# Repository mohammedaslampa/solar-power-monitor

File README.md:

# solar-power-monitor
monitoring solar power

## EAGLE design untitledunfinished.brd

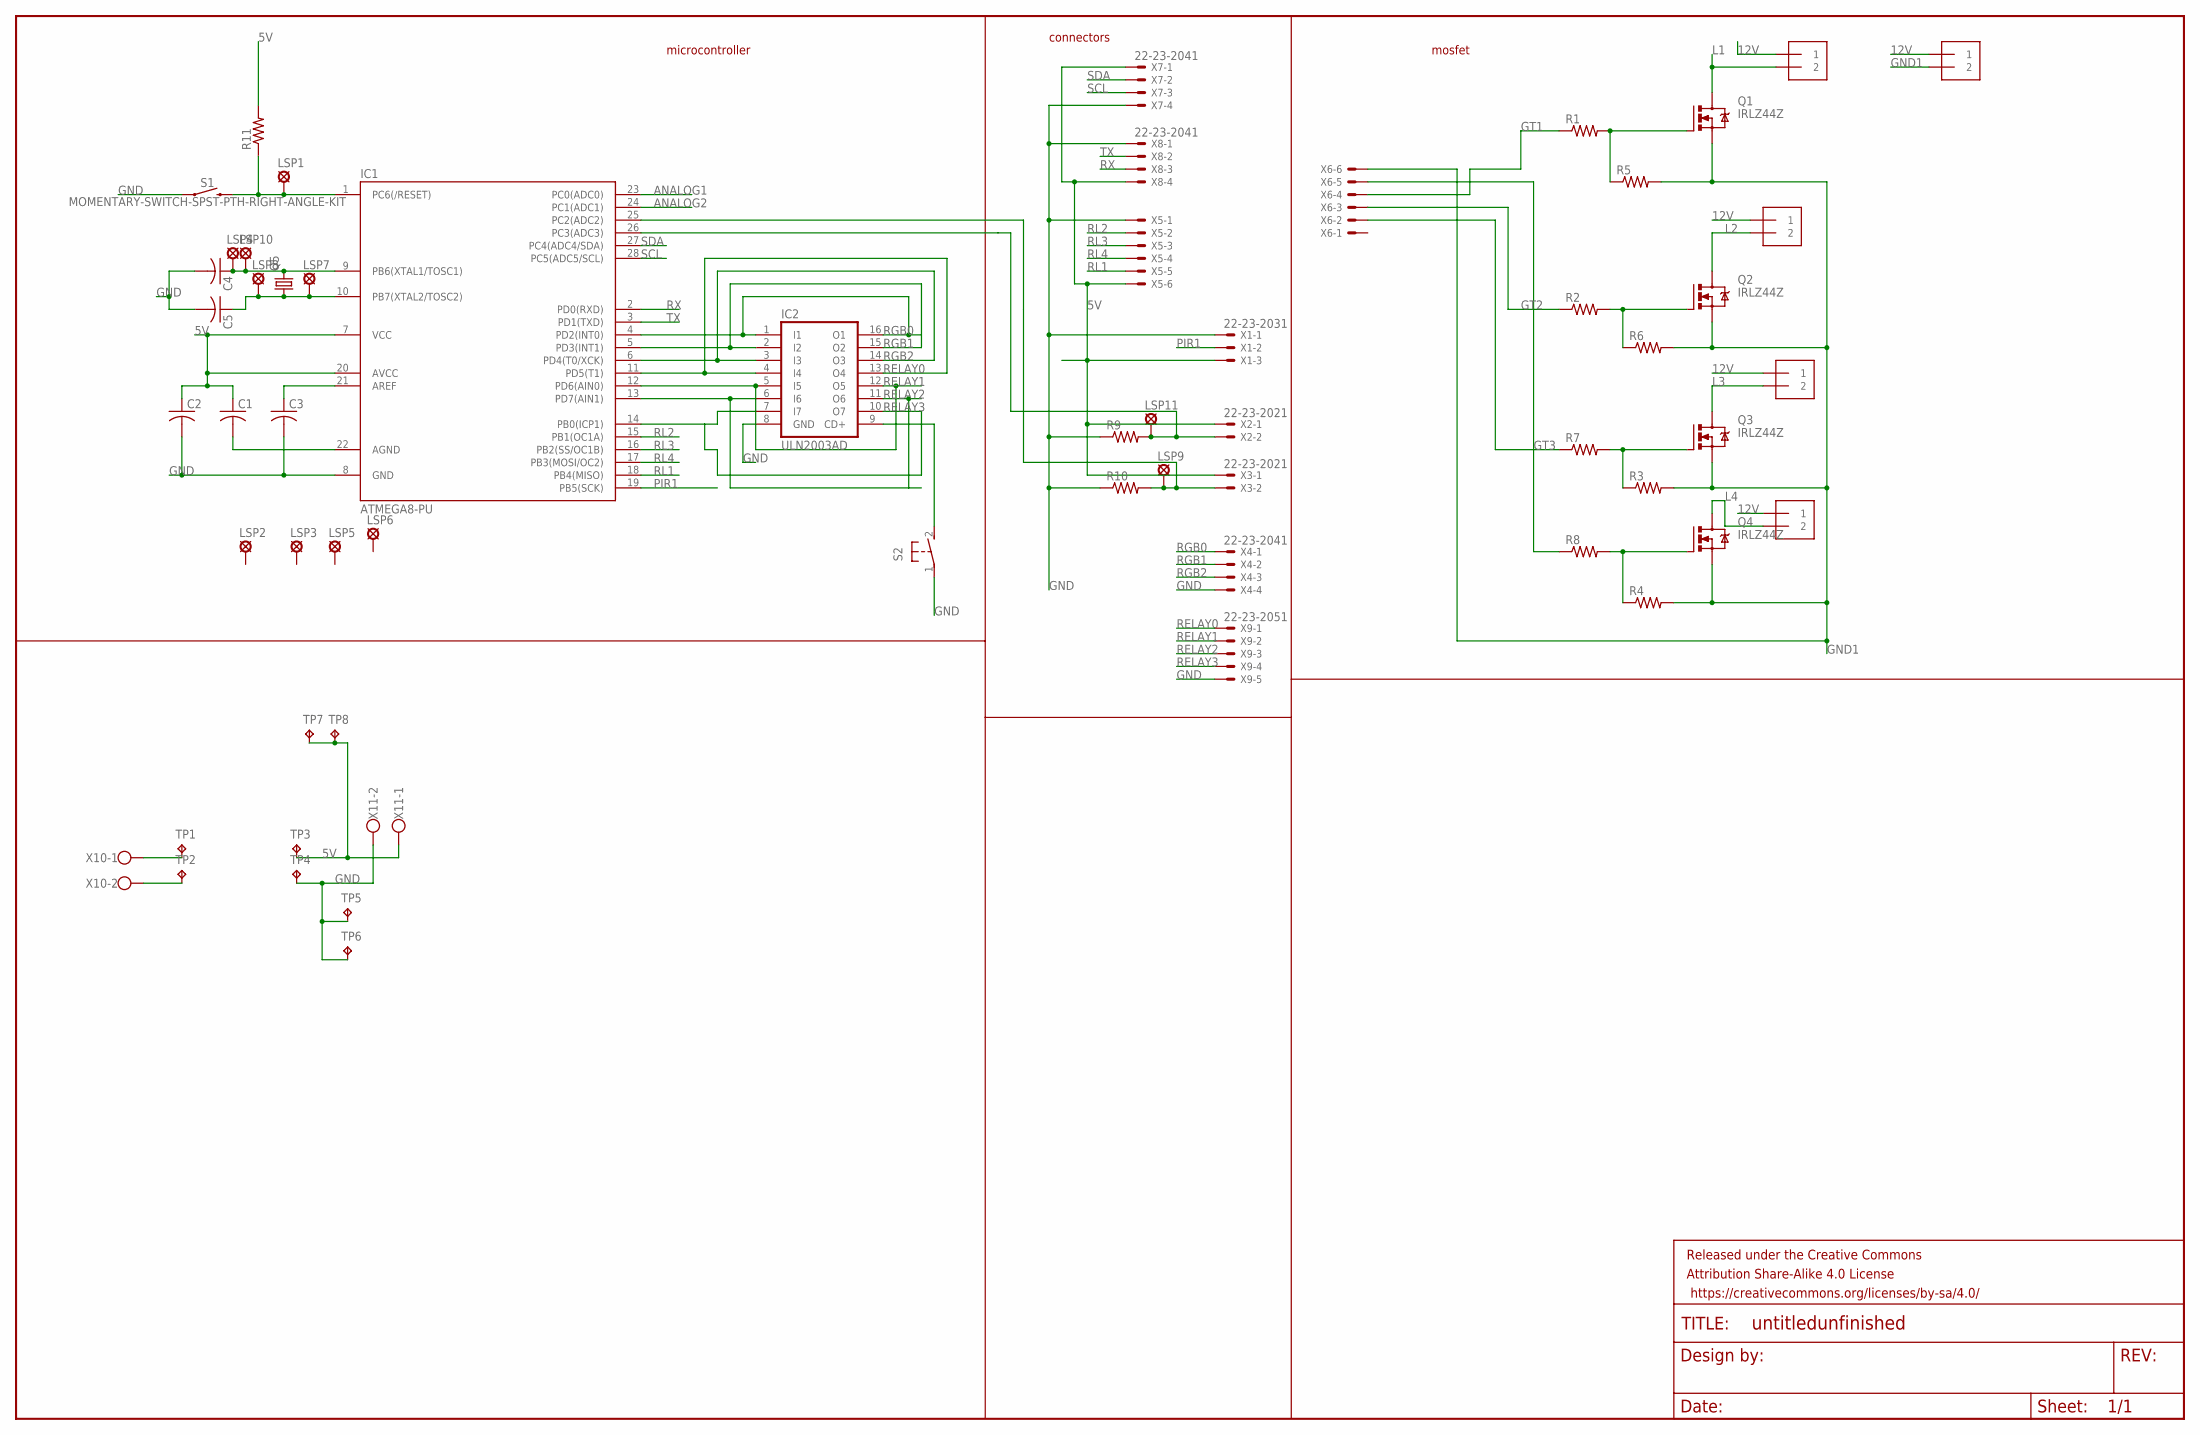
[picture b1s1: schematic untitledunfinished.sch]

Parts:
C1, C2, C3: C-US050-025X075; C050-025X075
C4, C5: C-US050-024X044; C050-024X044
FRAME1: FRAME-LEDGER; CREATIVE_COMMONS
IC1: ATMEGA8-PU; DIL28-3
IC2: ULN2003AD; SO16
J1, J2, J3, J4, J5: 1X2-3.5MM
LSP1, LSP2, LSP3, LSP4, LSP5, LSP6, LSP7, LSP8, LSP9, LSP10, LSP11: SE11
Q1, Q2, Q3, Q4: IRLZ44Z; TO220BH
Q5: CRYSTALHC49U-V; HC49U-V
R1, R2, R3, R4, R5, R6, R7, R8, R11: R-US_0207/10; 0207/10
R9, R10: R-US_0207/15; 0207/15
S1: MOMENTARY-SWITCH-SPST-PTH-RIGHT-ANGLE-KIT; TACTILE_SWITCH_PTH_RIGHT_ANGLE_KIT
S2: 31-XX; B3F-31XX
TP1, TP2, TP3, TP4: TPPAD1-20Y; P1-20Y
TP5, TP6, TP7, TP8: TPPAD1-13Y; P1-13Y
X1: 22-23-2031
X2, X3: 22-23-2021
X4, X7, X8: 22-23-2041
X5, X6: 22-23-2061
X9: 22-23-2051
X10, X11: W237-102

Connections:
5V: C1.1, C2.1, IC1.7 (VCC), IC1.20 (AVCC), R11.2, TP3.TP, TP7.TP, TP8.TP, X1.3, X2.1, X3.1, X5.6, X7.1, X8.4, X11.1
12V: J1.1, J2.1, J3.1, J4.1, J5.1
ANALOG1: IC1.23 (PC0(ADC0))
ANALOG2: IC1.24 (PC1(ADC1))
GND: C2.2, C3.2, C4.2, C5.2, IC1.8 (GND), IC2.8 (GND), R9.1, R10.1, S1.1, S2.1, TP4.TP, TP5.TP, TP6.TP, X1.1, X4.4, X5.1, X7.4, X8.1, X9.5, X11.2
GND1: J5.2, Q1.S, Q2.S, Q3.S, Q4.S, R3.2, R4.2, R5.2, R6.2, X6.6
GT1: R1.1, X6.4
GT2: R2.1, X6.3
GT3: R7.1, X6.2
L1: J1.2, Q1.D
L2: J2.2, Q2.D
L3: J3.2, Q3.D
L4: J4.2, Q4.D
unnamed: Q1.G, R1.2, R5.1
unnamed: R8.1, X6.5
unnamed: Q2.G, R2.2, R6.1
unnamed: C1.2, IC1.22 (AGND)
unnamed: Q3.G, R3.1, R7.2
unnamed: C3.1, IC1.21 (AREF)
unnamed: Q4.G, R4.1, R8.2
unnamed: TP1.TP, X10.1
unnamed: IC1.25 (PC2(ADC2)), LSP9.MP, R10.2, X3.2
unnamed: IC1.1 (PC6(/RESET)), LSP1.MP, R11.1, S1.2
unnamed: C4.1, IC1.9 (PB6(XTAL1/TOSC1)), LSP4.MP, LSP10.MP, Q5.2
unnamed: C5.1, IC1.10 (PB7(XTAL2/TOSC2)), LSP7.MP, LSP8.MP, Q5.1
unnamed: IC2.9 (CD+), S2.2 (S)
unnamed: IC1.26 (PC3(ADC3)), LSP11.MP, R9.2, X2.2
unnamed: TP2.TP, X10.2
PIR1: IC1.19 (PB5(SCK)), X1.2
RELAY0: IC1.11 (PD5(T1)), IC2.4 (I4), IC2.13 (O4), X9.1
RELAY1: IC1.12 (PD6(AIN0)), IC2.5 (I5), IC2.12 (O5), X9.2
RELAY2: IC1.13 (PD7(AIN1)), IC2.6 (I6), IC2.11 (O6), X9.3
RELAY3: IC1.14 (PB0(ICP1)), IC2.7 (I7), IC2.10 (O7), X9.4
RGB0: IC1.4 (PD2(INT0)), IC2.1 (I1), IC2.16 (O1), X4.1
RGB1: IC1.5 (PD3(INT1)), IC2.2 (I2), IC2.15 (O2), X4.2
RGB2: IC1.6 (PD4(T0/XCK)), IC2.3 (I3), IC2.14 (O3), X4.3
RL1: IC1.18 (PB4(MISO)), X5.5
RL2: IC1.15 (PB1(OC1A)), X5.2
RL3: IC1.16 (PB2(SS/OC1B)), X5.3
RL4: IC1.17 (PB3(MOSI/OC2)), X5.4
RX: IC1.2 (PD0(RXD)), X8.3
SCL: IC1.28 (PC5(ADC5/SCL)), X7.3
SDA: IC1.27 (PC4(ADC4/SDA)), X7.2
TX: IC1.3 (PD1(TXD)), X8.2

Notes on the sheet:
microcontroller
mosfet
connectors

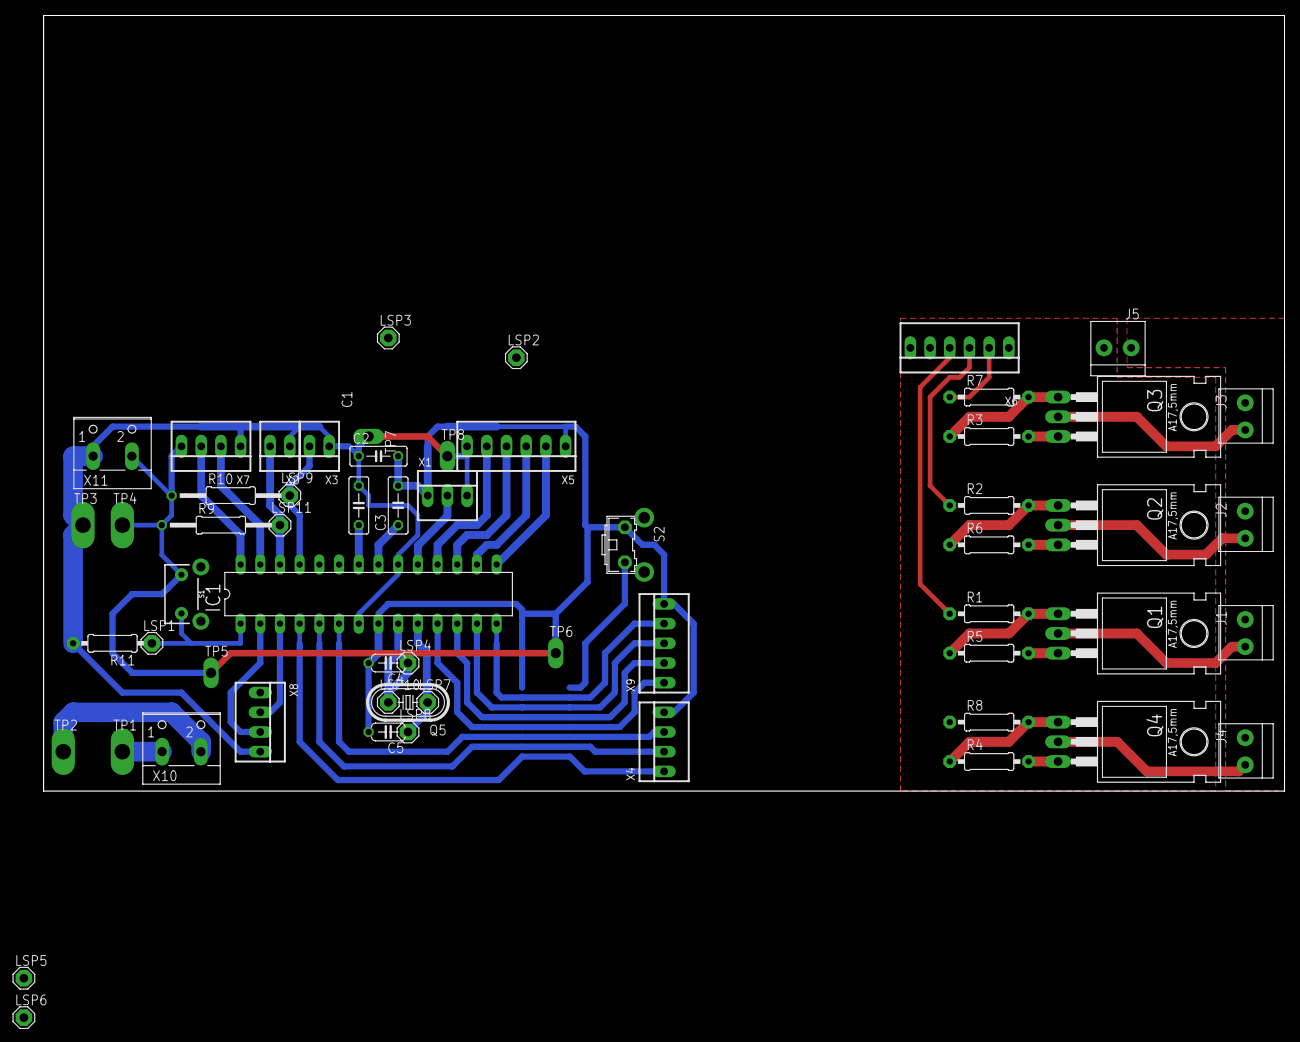
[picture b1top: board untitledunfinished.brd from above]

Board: 2 copper layers, 160.0 x 100.0 mm, 61 parts (1 on the bottom side), 42 nets.

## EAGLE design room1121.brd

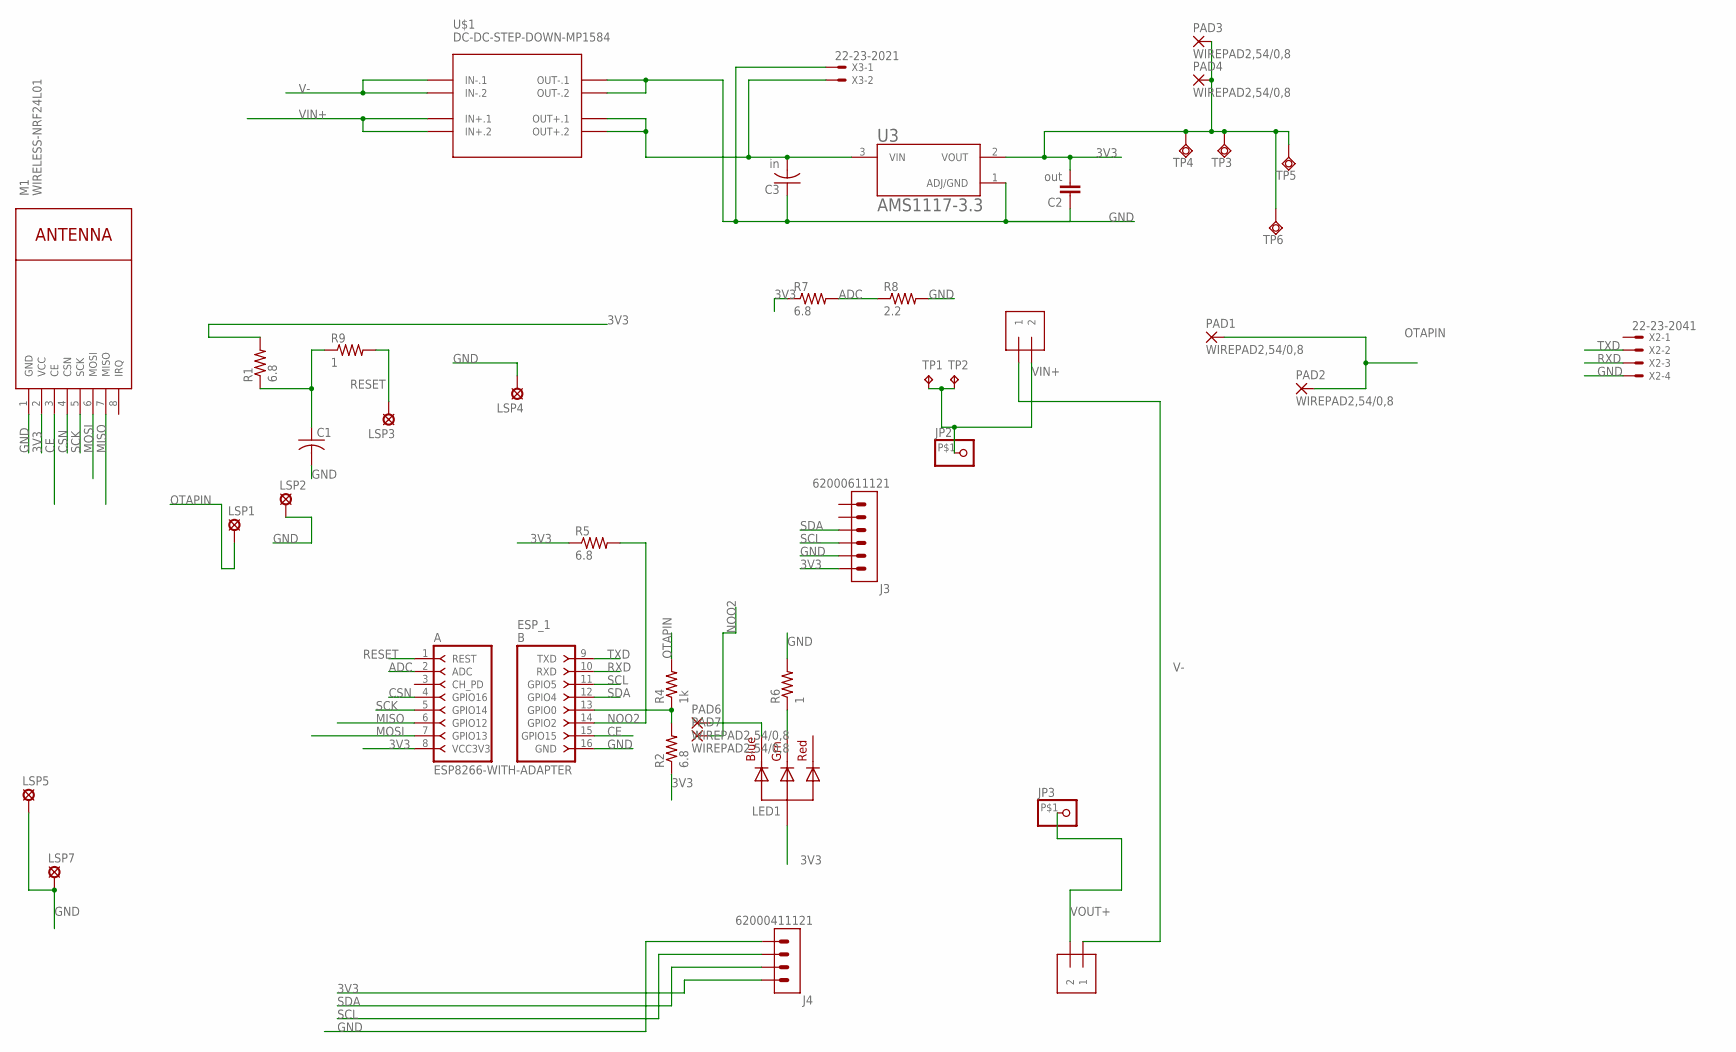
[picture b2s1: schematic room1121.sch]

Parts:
C1: C-US025-040X050; C025-040X050
C2: out; C025-060X050
C3: in; C075-032X103
ESP_1: ESP8266-WITH-ADAPTER; ESP8266-ADAPTER
J1, J2: 1X2-3.5MM
J3: 62000611121
J4: 62000411121
JP2, JP3: PINHD-1X1-BIGPOGO; 1X1-BIGPOGO
LED1: RGBLED_CA-5MM; LED5MMRGB
LSP1, LSP2, LSP3, LSP4: SE14
LSP5, LSP7: MCS10B
M1: WIRELESS-NRF24L01
PAD1, PAD2, PAD3, PAD4, PAD6, PAD7: WIREPAD2,54/0,8; 2,54/0,8
R1, R2: 6.8; 0207/15
R4: 1k; 0207/15
R5, R7: 6.8; 0207/12
R6: 1; 0207/10
R8: 2.2; 0207/15
R9: 1; 0207/12
TP1, TP2: TPPAD1-20Y; P1-20Y
TP3, TP4, TP5, TP6: TPSQPAD1-13Y; P1-13Y
U3: AMS1117-3.3; SOT229P700X180-4N
U$1: DC-DC-STEP-DOWN-MP1584
X2: 22-23-2041
X3: 22-23-2021

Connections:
3V3: C2.2, ESP_1.8 (VCC3V3), J3.1, J4.1, LED1.2 (VCC), M1.2 (VCC), PAD3.1, PAD4.1, R1.2, R2.1, R5.1, R7.1, TP3.TP, TP4.TP, TP5.TP, TP6.TP, U3.2 (VOUT)
ADC: ESP_1.2 (ADC), R7.2, R8.1
CE: ESP_1.15 (GPIO15), M1.3 (CE)
CSN: ESP_1.4 (GPIO16), M1.4 (CSN)
GND: C1.2, C2.1, C3.1, ESP_1.16 (GND), J3.2, J4.4, LSP2.MP, LSP4.MP, LSP5.MP, LSP7.MP, M1.1 (GND), R6.2, R8.2, U3.1 (ADJ/GND), U$1.OUT-.1, U$1.OUT-.2, X2.4, X3.1
MISO: ESP_1.6 (GPIO12), M1.7 (MISO)
MOSI: ESP_1.7 (GPIO13), M1.6 (MOSI)
unnamed: LED1.3 (GREEN), R6.1
unnamed: ESP_1.13 (GPIO0), R2.2, R4.1
unnamed: C3.2, U3.3 (VIN), U$1.OUT+.1, U$1.OUT+.2, X3.2
unnamed: LED1.4 (BLUE), PAD6.1
unnamed: LSP3.MP, R9.2
NOO2: ESP_1.14 (GPIO2), PAD7.1, R5.2
OTAPIN: LSP1.MP, PAD1.1, PAD2.1, R4.2
RESET: C1.1, ESP_1.1 (REST), R1.1, R9.1
RXD: ESP_1.10 (RXD), X2.3
SCK: ESP_1.5 (GPIO14), M1.5 (SCK)
SCL: ESP_1.11 (GPIO5), J3.3, J4.3
SDA: ESP_1.12 (GPIO4), J3.4, J4.2
TXD: ESP_1.9 (TXD), X2.2
V-: J1.1, J2.1, U$1.IN-.1, U$1.IN-.2
VIN+: J2.2, JP2.P$1, TP1.TP, TP2.TP, U$1.IN+.1, U$1.IN+.2
VOUT+: J1.2, JP3.P$1

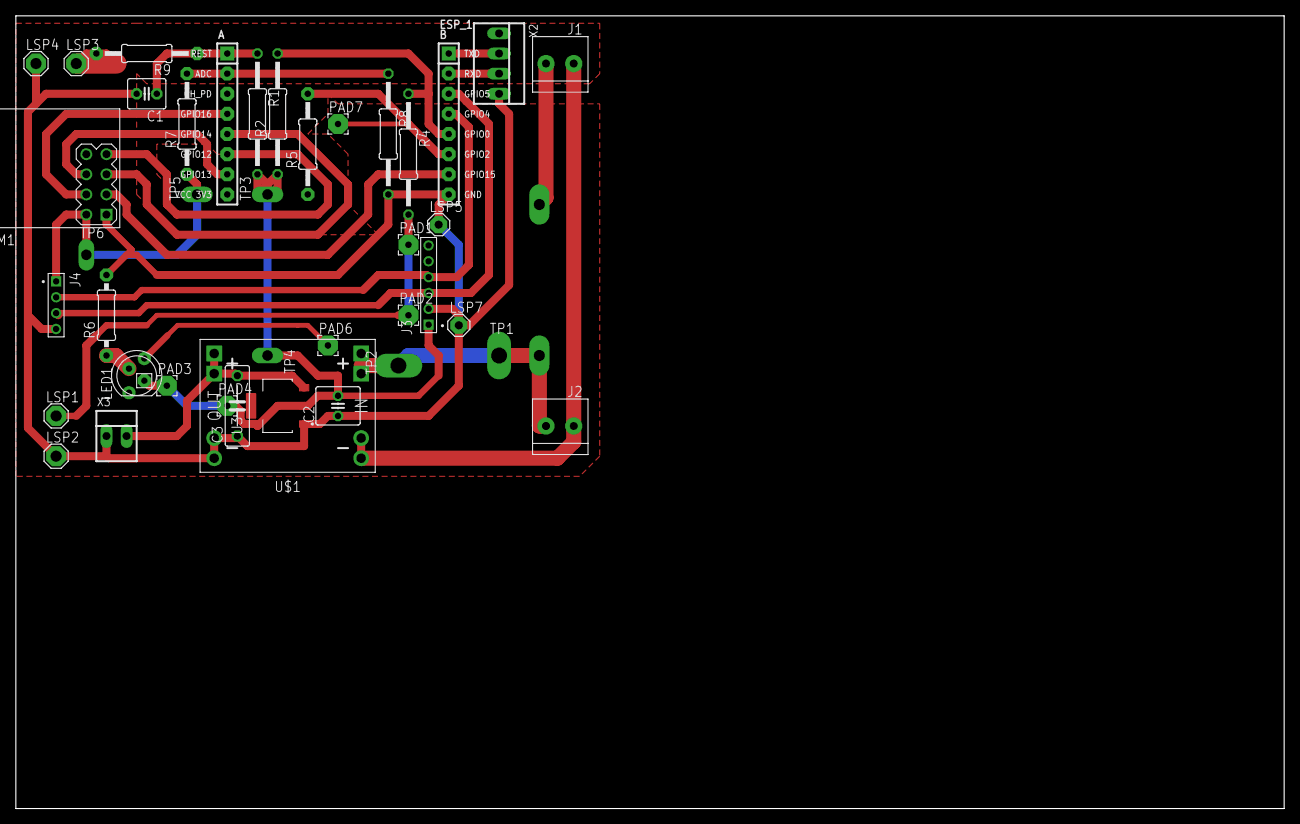
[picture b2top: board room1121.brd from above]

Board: 2 copper layers, 160.0 x 100.0 mm, 42 parts (0 on the bottom side), 23 nets.

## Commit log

2021-04-17 main sensor code
    main sensor containing ina219 and nrf24l
2021-04-17 ssid and channel credentials
    SSID and channel credentials for main-sensor-code
2021-04-17 receiver circuit code
    receiver circuit containing relays and nrf24l01
2021-04-25 room1121
    schematic and pcb layout for power monitor
2021-05-07 i2c addon for esp
    atmega 8 with 4 mosfet
2021-05-07 i2c addon code
    code for atmega 8 i2c addon for esp
2021-09-01 Create LICENSE

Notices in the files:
parts and their libraries:
diy-modules: Released under the Creative Commons Attribution 4.0 International License: http://creativecommons.org/licenses/by/4.0
SparkFun-Aesthetics: Licensing: Creative Commons ShareAlike 4.0 International - https://creativecommons.org/licenses/by-sa/4.0
